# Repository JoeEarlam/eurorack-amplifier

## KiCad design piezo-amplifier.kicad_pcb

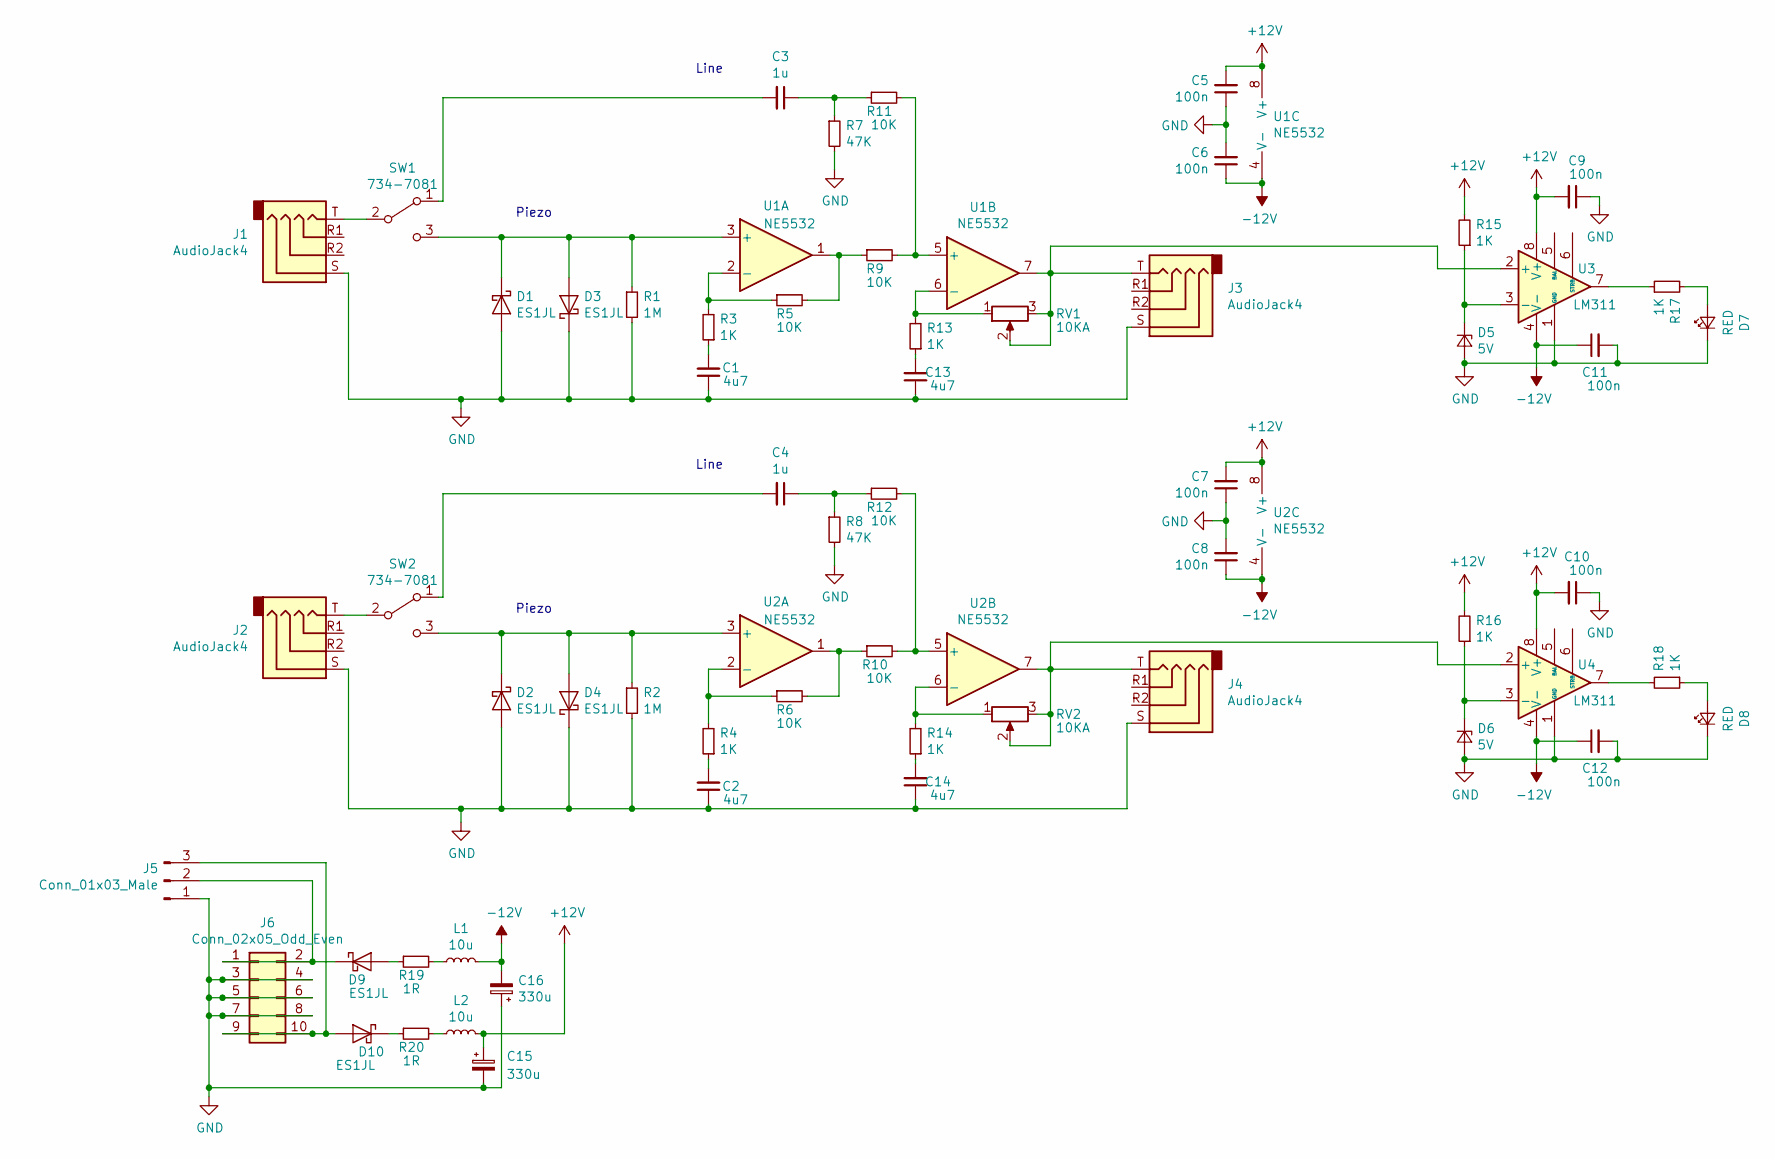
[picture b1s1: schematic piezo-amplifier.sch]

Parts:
C1, C2, C13, C14: 4u7; C_0805_2012Metric
C3, C4: 1u; C_0805_2012Metric
C5, C6, C7, C8, C9, C10, C11, C12: 100n; C_0805_2012Metric
C15, C16: 330u; CP_Elec_8x10
D1, D2, D3, D4, D9, D10: ES1JL; D_SOD-123
D5, D6: 5V; D_SOD-123
D7: RED; LED_0805_2012Metric
D8: RED; LED_1206_3216Metric
J1, J2, J3, J4: AudioJack4; Jack_3.5mm_PJ320D_TH
J5: Conn_01x03_Male; JST_XH_S3B-XH-A-1_1x03_P2.50mm_Horizontal
J6: Conn_02x05_Odd_Even; PinHeader_2x05_P2.54mm_Vertical
L1, L2: 10u; L_0805_2012Metric
R1, R2: 1M; R_0805_2012Metric
R3, R4, R13, R14, R15, R16, R17, R18: 1K; R_0805_2012Metric
R5, R6, R9, R10, R11, R12: 10K; R_0805_2012Metric
R7, R8: 47K; R_0805_2012Metric
R19, R20: 1R; R_0805_2012Metric
RV1, RV2: 10KA; Potentiometer_Alps_RK163_Single_Horizontal
SW1, SW2: 734-7081; RS-toggle-734-7081
U1, U2: NE5532; SOIC-8_3.9x4.9mm_P1.27mm
U3, U4: LM311; SOIC-8_3.9x4.9mm_P1.27mm

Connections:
+12V: C5.2, C7.2, C9.2, C10.2, C15.1, L2.2, R15.2, R16.2, U1.8 (V+), U2.8 (V+), U3.8 (V+), U4.8 (V+)
-12V: C6.1, C8.1, C11.1, C12.1, C16.2, L1.2, U1.4 (V-), U2.4 (V-), U3.4 (V-), U4.4 (V-)
GND: C1.1, C2.1, C5.1, C6.2, C7.1, C8.2, C9.1, C10.1, C11.2, C12.2, C13.1, C14.1, C15.2, C16.1, D1.2 (A), D2.2 (A), D3.1 (K), D4.1 (K), D5.2 (A), D6.2 (A), D7.1 (K), D8.1 (K), J1.S, J2.S, J3.S, J4.S, J5.1, J6.3, J6.4, J6.5, J6.6, J6.7, J6.8, R1.2, R2.2, R7.2, R8.2, U3.1 (GND), U4.1 (GND)
unnamed: C1.2, R3.1
unnamed: C2.2, R4.1
unnamed: C3.1, R7.1, R11.1
unnamed: C3.2, SW1.1 (A)
unnamed: C4.1, R8.1, R12.1
unnamed: C4.2, SW2.1 (A)
unnamed: C13.2, R13.1
unnamed: C14.2, R14.1
unnamed: D1.1 (K), D3.2 (A), R1.1, SW1.3 (C), U1.3 (+)
unnamed: D2.1 (K), D4.2 (A), R2.1, SW2.3 (C), U2.3 (+)
unnamed: D5.1 (K), R15.1, U3.3 (-)
unnamed: D6.1 (K), R16.1, U4.3 (-)
unnamed: D7.2 (A), R17.2
unnamed: D8.2 (A), R18.1
unnamed: D9.1 (K), J5.2, J6.1, J6.2
unnamed: D9.2 (A), R19.1
unnamed: D10.1 (K), R20.1
unnamed: D10.2 (A), J5.3, J6.9, J6.10
unnamed: J1.T, SW1.2 (B)
unnamed: J2.T, SW2.2 (B)
unnamed: J3.T, RV1.2, RV1.3, U1.7, U3.2 (+)
unnamed: J4.T, RV2.2, RV2.3, U2.7, U4.2 (+)
unnamed: L1.1, R19.2
unnamed: L2.1, R20.2
unnamed: R3.2, R5.1, U1.2 (-)
unnamed: R4.2, R6.1, U2.2 (-)
unnamed: R5.2, R9.1, U1.1
unnamed: R6.2, R10.1, U2.1
unnamed: R10.2, R12.2, U2.5 (+)
unnamed: R9.2, R11.2, U1.5 (+)
unnamed: R13.2, RV1.1, U1.6 (-)
unnamed: R14.2, RV2.1, U2.6 (-)
unnamed: R17.1, U3.7
unnamed: R18.2, U4.7

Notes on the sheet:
Line
Piezo

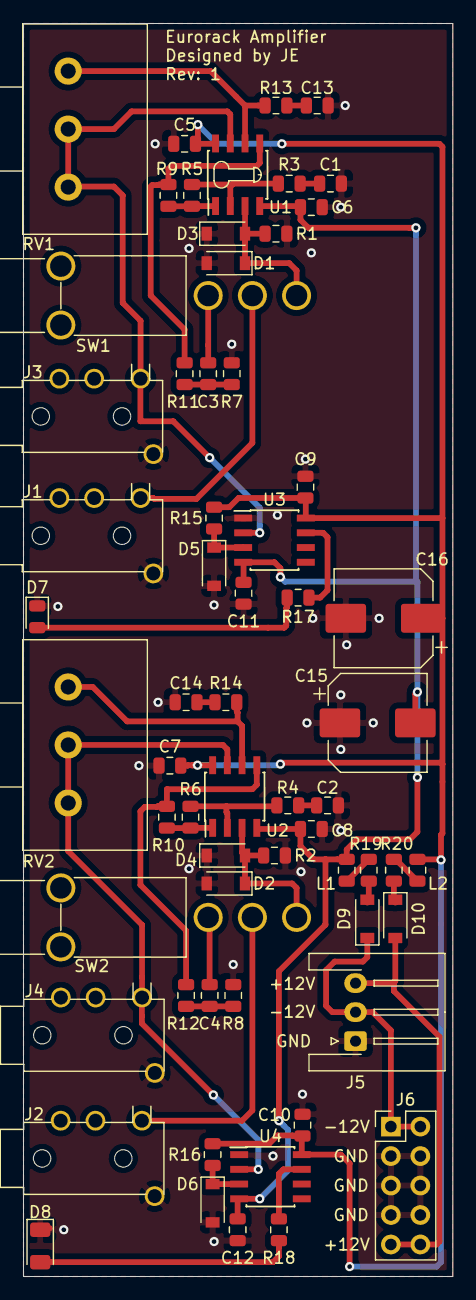
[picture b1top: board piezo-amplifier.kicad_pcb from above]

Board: 2 copper layers, 37.0 x 108.0 mm, 62 parts (0 on the bottom side), 37 nets.

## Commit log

2019-07-15 switched to SMD capacitors, minor layout and silkscreen changes
